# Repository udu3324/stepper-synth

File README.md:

# stepper-synth

An electronic instrument that uses stepper motors to make music. Powered by the esp32 ecosystem, it is a synthesizer with 3 octaves with velocity support using hall effect sensors. It is inspired by the musician/engineer [Love Hultén](https://www.youtube.com/@hulten1000).

## Why I Made This

There's so many electronic instruments that make sounds purely through cables and rely on other devices to output to them. Instead, what if I used the power of stepper motors to make sound and create a standalone device? I notice how harmonic these motors could be while 3d printing, they sometimes have a noticable pattern and variable pitch that can be utilized.

## Photos

## PCB

## Schematics

## Bill of Materials

Sadly I was aiming for tier 2 budget but didn't realize how much tariffs and shipping would push me out of it 😭

Interactive Link: [google sheets](https://docs.google.com/spreadsheets/d/12KobohwvsCrDZkVZn1qAy473UDQfyoO-3Iqs66wPygc/edit?usp=sharing)

|Part                     |Cost   |Count|Count Cost|Note                                                     |Status |Link                                                                                                                                                             |
|-------------------------|-------|-----|----------|---------------------------------------------------------|-------|-----------------------------------------------------------------------------------------------------------------------------------------------------------------|
|Regular Switches         |       |2    |0         |                                                         |On hand|https://divinikey.com/collections/linear-switches                                                                                                                |
|Hall Effect Switches     |$13.50 |2    |$27.00    |18x per                                                  |       |https://divinikey.com/collections/hall-effect-switches/products/gateron-magnetic-genty-he-switches                                                               |
|Rotary Encoder           |       |3    |0         |                                                         |On hand|https://www.mouser.com/ProductDetail/Alps-Alpine/EC11E183440C?qs=YMSFtX0bdJC6PoDF7K4k%252Bg%3D%3D                                                                |
|Button                   |       |1    |0         |                                                         |On hand|https://www.digikey.com/en/products/detail/te-connectivity-alcoswitch-switches/1825910-6/1632536                                                                 |
|WS2812                   |$0.80  |8    |$6.40     |neopixels                                                |       |https://www.mouser.com/ProductDetail/SparkFun/COM-24837?qs=dbcCsuKDzFUNFvBH5VYBTw%3D%3D                                                                          |
|LRS-350-24               |       |1    |0         |power supply                                             |On hand|https://www.digikey.com/en/products/detail/mean-well-usa-inc/LRS-350-24/7705034                                                                                  |
|IEC320 C14 Switch        |       |1    |0         |cable input                                              |On hand|https://www.aliexpress.us/item/3256804155743663.html                                                                                                             |
|Screw Terminal           |$0.35  |1    |$0.35     |                                                         |       |https://www.mouser.com/ProductDetail/Same-Sky/TB002-500-02BE?qs=vLWxofP3U2x9716kcgva%2Fw%3D%3D                                                                   |
|Nema 17 0.8 Motors       |       |4    |$0.00     |reused prusas                                            |On hand|https://www.omc-stepperonline.com/nema-17-bipolar-0-9deg-46ncm-65-1oz-in-2a-2-9v-42x42x48mm-4-wires-17hm19-2004s                                                 |
|ESP32-S3-WROOM-2         |$11.87 |1    |$11.87    |microcontroller                                          |       |https://www.mouser.com/ProductDetail/Espressif-Systems/ESP32-S3-WROOM-2-N32R16V?qs=%252BHhoWzUJg4Kf%2FwmS40wg%252BQ%3D%3D                                        |
|Solder Paste Syringe     |$16.95 |1    |$16.95    |mine dried out                                           |       |https://www.mouser.com/ProductDetail/Chip-Quik/TS391LT?qs=1mbolxNpo8dzjCIcP7S2Kg%3D%3D                                                                           |
|150uF Polarized Capacitor|$1.40  |4    |$5.60     |                                                         |       |https://www.mouser.com/ProductDetail/Panasonic/EEH-AZA1E151B?qs=sGAEpiMZZMsh%252B1woXyUXj7hTFrnMyX90Ysfyv/7vmlA%3D                                               |
|Female Pin Headers       |$0.84  |2    |$1.68     |                                                         |       |https://www.mouser.com/ProductDetail/Samtec/CES-102-02-G-S?qs=0lQeLiL1qyY%2FrwXtinpohw%3D%3D                                                                     |
|Hot-swap Switch Plug     |       |2    |0         |                                                         |On hand|https://www.gateron.com/products/gateron-low-profile-switch-hot-swap-pcb-socket?srsltid=AfmBOop0aFTt__A_sBY2D5LC6GJteiDSPO9H3qEt2M2Dhil_s2AUwsRR&VariantsId=10234|
|M3x5mm Screws            |       |18   |          |                                                         |On hand|https://www.moddiy.com/products/1264/M3.0-x-5mm-Black-Screws-(KM3X5).html?srsltid=AfmBOorXbTDS16CG3UQ8tCHJn64vKhPv2bQRUskhtAbTRuyfojuJ6yEs_D8                    |
|                         |       |     |          |                                                         |       |                                                                                                                                                                 |
|PCB Prototype            |$12.20 |     |          |                                                         |       |                                                                                                                                                                 |
|PCBA                     |$90.68 |     |          |6 extended parts only                                    |       |                                                                                                                                                                 |
|Merchandise Total        |$102.88|     |          |pcb + pcba                                               |       |                                                                                                                                                                 |
|Shipping Estimate        |$55.24 |     |          |                                                         |       |                                                                                                                                                                 |
|Duties & Taxes (US)      |$46.30 |     |          |                                                         |       |                                                                                                                                                                 |
|Sales Tax                |$13.04 |     |          |                                                         |       |                                                                                                                                                                 |
|Grand Total              |$217.46|     |          |only count this                                          |       |                                                                                                                                                                 |
|                         |       |     |          |                                                         |       |                                                                                                                                                                 |
|                         |$217.46|     |69.85     |                                                         |       |                                                                                                                                                                 |
|                         |       |     |          |                                                         |       |                                                                                                                                                                 |
|Needed for Grant         |$287.31|     |          |not including shipping and taxes from mouser/divinikey!!!|       |                                                                                                                                                                 |
|                         |       |     |          |though mouser shipping should be really low              |       |                                                                                                                                                                 |

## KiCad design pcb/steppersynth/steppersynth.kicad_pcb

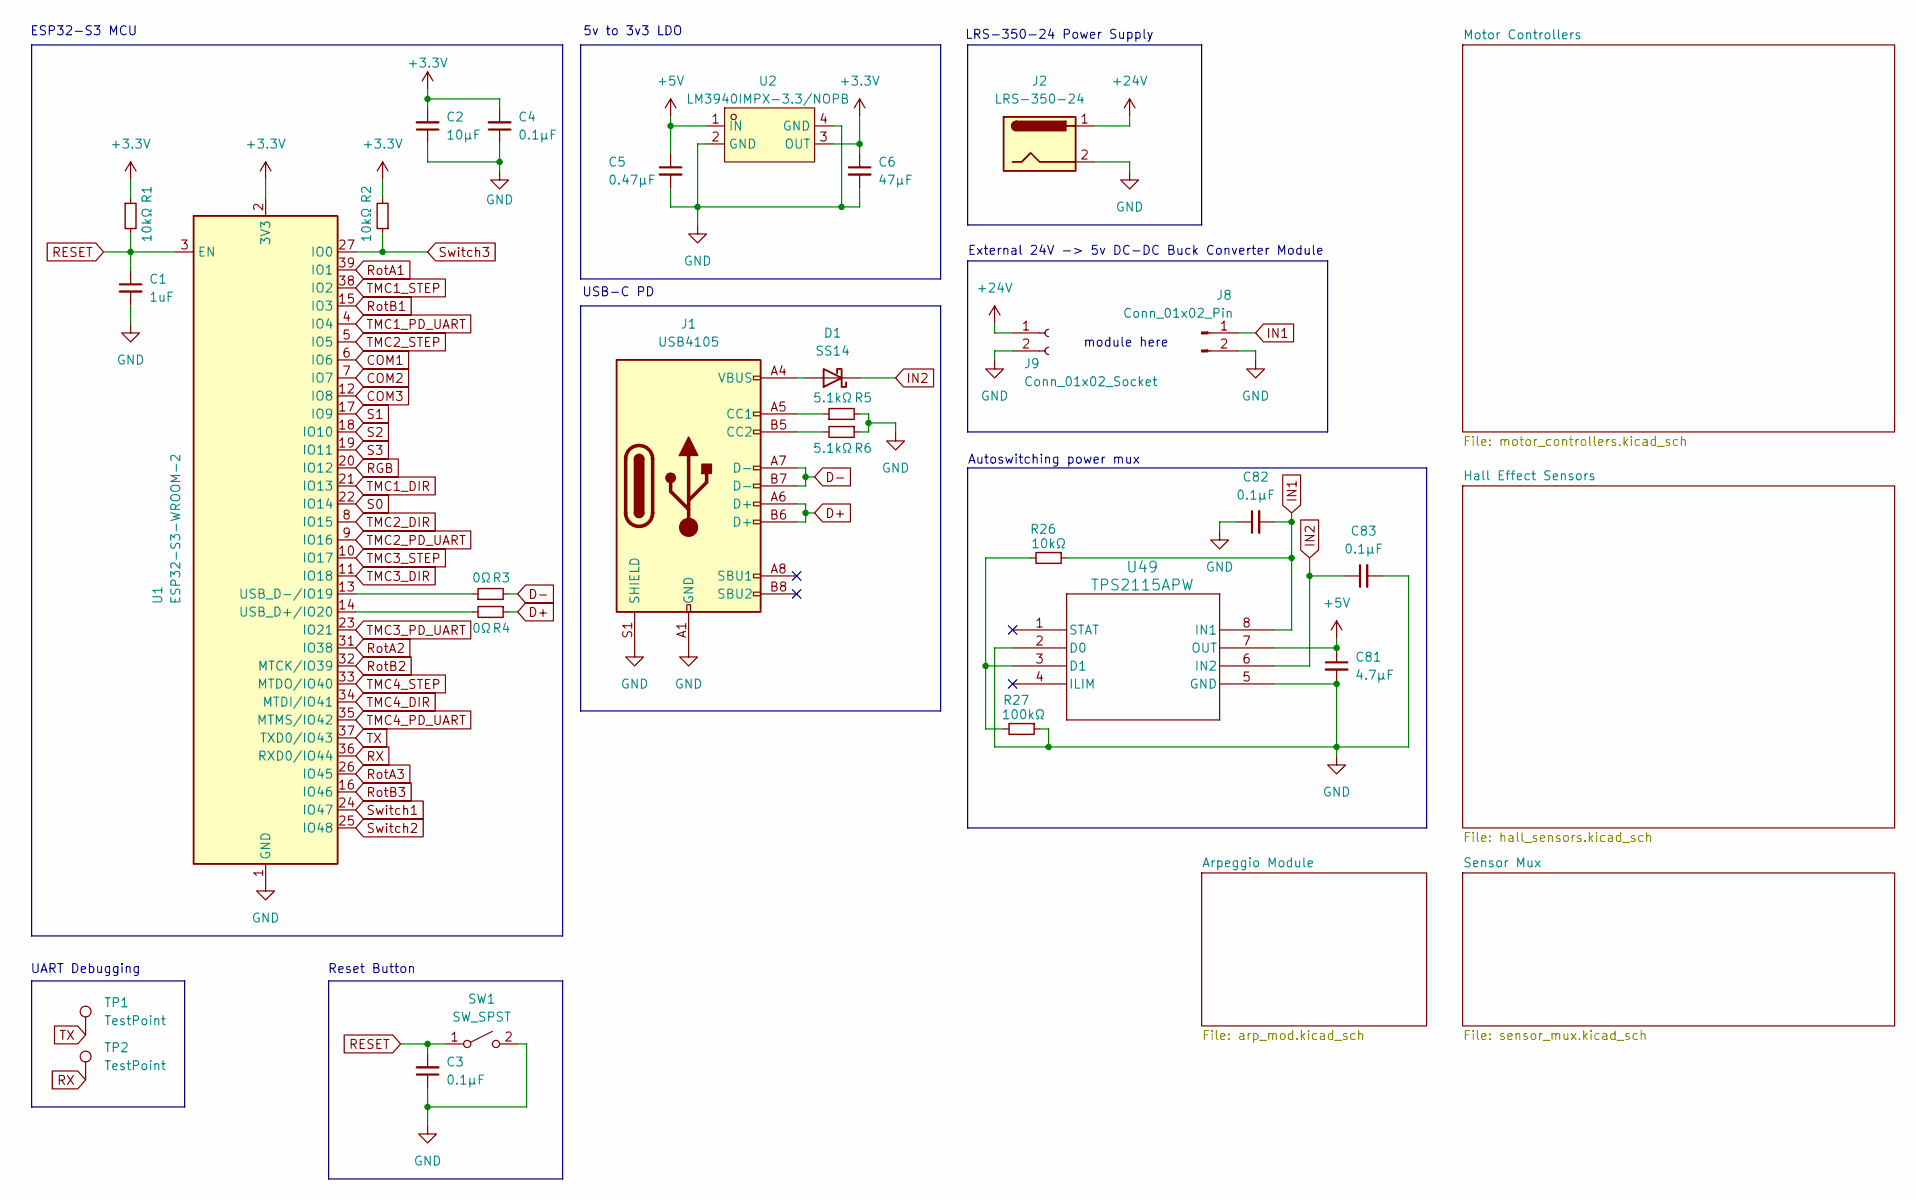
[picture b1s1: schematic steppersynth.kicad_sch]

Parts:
C1: 1uF; C_0805_2012Metric
C2: 10μF; C_0805_2012Metric
C3, C4, C82, C83: 0.1μF; C_0805_2012Metric
C5: 0.47μF; C_0805_2012Metric
C6: 47μF; C_0805_2012Metric
C81: 4.7μF; C_0805_2012Metric
D1: SS14; D_SMA
J1: USB4105; USB_C_Receptacle_GCT_USB4105-xx-A_16P_TopMnt_Horizontal
J2: LRS-350-24; TerminalBlock_MetzConnect_Type055_RT01502HDWU_1x02_P5.00mm_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
J8: Conn_01x02_Pin; PinSocket_1x02_P2.54mm_Vertical
J9: Conn_01x02_Socket; PinSocket_1x02_P2.54mm_Vertical
R1, R2, R26: 10kΩ; R_0805_2012Metric
R3, R4: 0Ω; R_0805_2012Metric
R5, R6: 5.1kΩ; R_0805_2012Metric
R27: 100kΩ; R_0805_2012Metric
SW1: SW_SPST; SW_PUSH_6mm
TP1, TP2: TestPoint; MountingHole_3.2mm_M3_Pad
U1: ESP32-S3-WROOM-2
U2: LM3940IMPX-3.3/NOPB; SOT-223-4_L6.5-W3.5-P2.30-LS7.0-BR; LCSC Part C544820
U49: TPS2115APW; PW8

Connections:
+3.3V: C2.2, C4.2, C6.1, R1.1, R2.2, U1.2 (3V3), U2.3 (OUT); also elsewhere on the board
+5V: C5.1, C81.1, U2.1 (IN), U49.7 (OUT); also elsewhere on the board
+24V: J2.1, J9.1; also elsewhere on the board
COM1: U1.6 (IO6); also elsewhere on the board
COM2: U1.7 (IO7); also elsewhere on the board
COM3: U1.12 (IO8); also elsewhere on the board
D+: J1.A6 (D+), J1.B6 (D+), R4.1
D-: J1.A7 (D-), J1.B7 (D-), R3.2
GND: C1.2, C2.1, C3.1, C4.1, C5.2, C6.2, C81.2, C82.1, C83.2, J1.A1 (GND), J1.A12 (GND), J1.B1 (GND), J1.B12 (GND), J1.S1 (SHIELD), J2.2, J8.2, J9.2, R5.2, R6.1, R27.1, SW1.2 (B), U1.1 (GND), U1.40 (GND), U1.41 (GND), U2.2 (GND), U2.4 (GND), U49.2 (D0), U49.5 (GND); also elsewhere on the board
IN1: C82.2, J8.1, R26.1, U49.8 (IN1)
IN2: C83.1, D1.1 (K), U49.6 (IN2)
unnamed: D1.2 (A), J1.A4 (VBUS), J1.A9 (VBUS), J1.B4 (VBUS), J1.B9 (VBUS)
unnamed: J1.A5 (CC1), R5.1
unnamed: J1.B5 (CC2), R6.2
unnamed: R4.2, U1.14 (USB_D+/IO20)
unnamed: R3.1, U1.13 (USB_D-/IO19)
unnamed: R26.2, R27.2, U49.3 (D1)
RESET: C1.1, C3.2, R1.2, SW1.1 (A), U1.3 (EN)
RGB: U1.20 (IO12); also elsewhere on the board
RX: TP2.1, U1.36 (RXD0/IO44)
RotA1: U1.39 (IO1); also elsewhere on the board
RotA2: U1.31 (IO38); also elsewhere on the board
RotA3: U1.26 (IO45); also elsewhere on the board
RotB1: U1.15 (IO3); also elsewhere on the board
RotB2: U1.32 (MTCK/IO39); also elsewhere on the board
RotB3: U1.16 (IO46); also elsewhere on the board
S0: U1.22 (IO14); also elsewhere on the board
S1: U1.17 (IO9); also elsewhere on the board
S2: U1.18 (IO10); also elsewhere on the board
S3: U1.19 (IO11); also elsewhere on the board
Switch1: U1.24 (IO47); also elsewhere on the board
Switch2: U1.25 (IO48); also elsewhere on the board
Switch3: R2.1, U1.27 (IO0); also elsewhere on the board
TMC1_DIR: U1.21 (IO13); also elsewhere on the board
TMC1_PD_UART: U1.4 (IO4); also elsewhere on the board
TMC1_STEP: U1.38 (IO2); also elsewhere on the board
TMC2_DIR: U1.8 (IO15); also elsewhere on the board
TMC2_PD_UART: U1.9 (IO16); also elsewhere on the board
TMC2_STEP: U1.5 (IO5); also elsewhere on the board
TMC3_DIR: U1.11 (IO18); also elsewhere on the board
TMC3_PD_UART: U1.23 (IO21); also elsewhere on the board
TMC3_STEP: U1.10 (IO17); also elsewhere on the board
TMC4_DIR: U1.34 (MTDI/IO41); also elsewhere on the board
TMC4_PD_UART: U1.35 (MTMS/IO42); also elsewhere on the board
TMC4_STEP: U1.33 (MTDO/IO40); also elsewhere on the board
TX: TP1.1, U1.37 (TXD0/IO43)

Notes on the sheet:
5v to 3v3 LDO
LRS-350-24 Power Supply
ESP32-S3 MCU
Reset Button
Autoswitching power mux
USB-C PD
module here
UART Debugging
External 24V -> 5v DC-DC Buck Converter Module

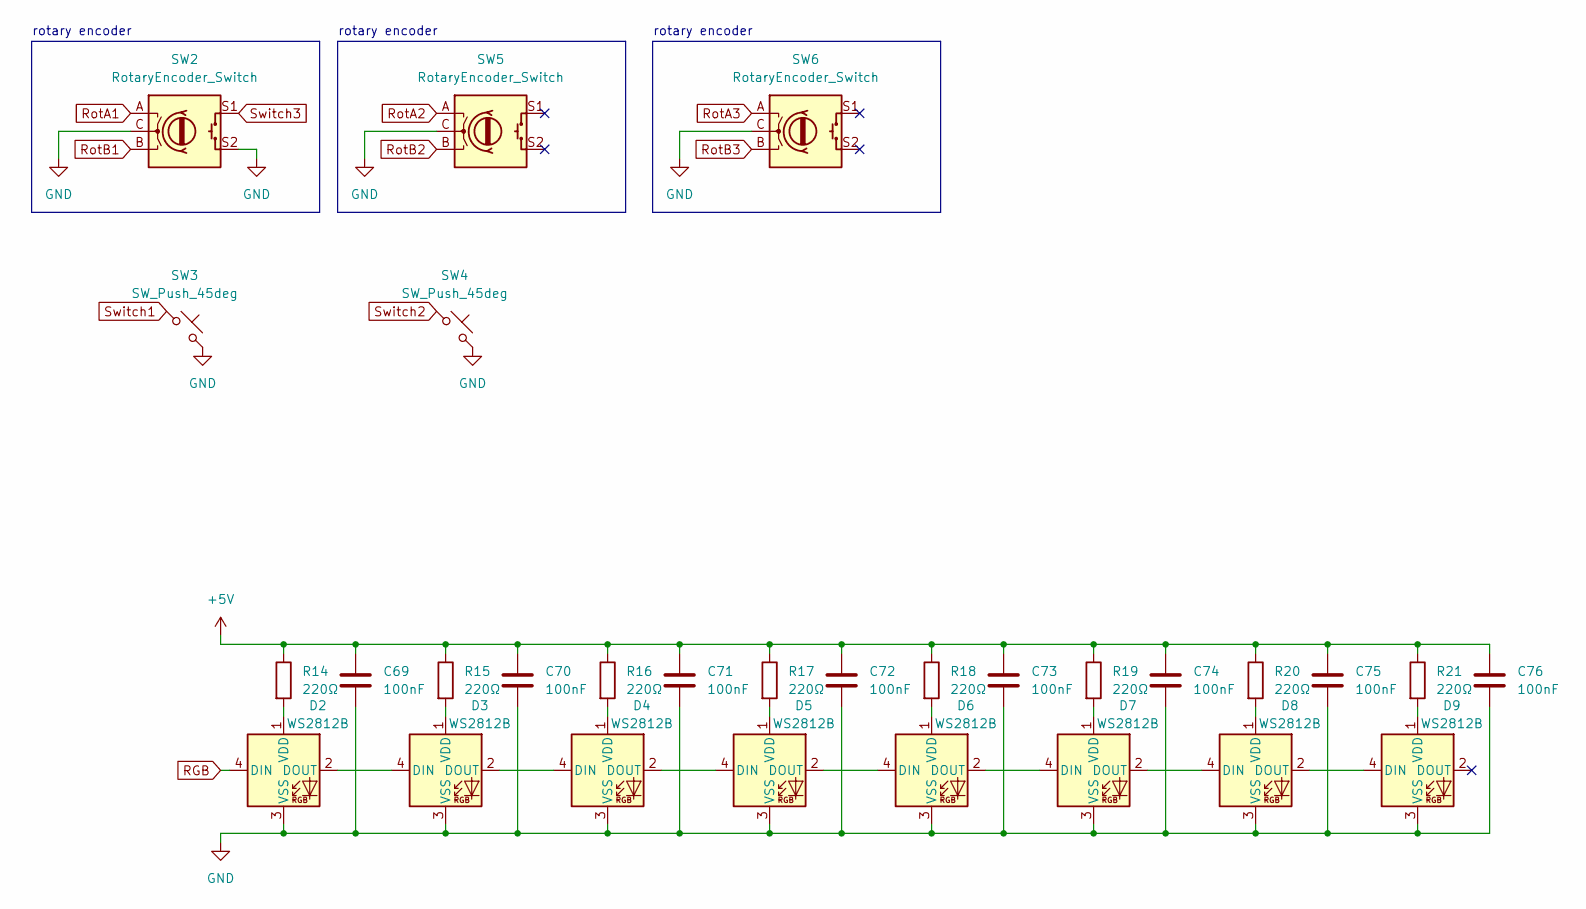
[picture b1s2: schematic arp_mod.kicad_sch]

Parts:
C69, C70, C71, C72, C73, C74, C75, C76: 100nF; C_0805_2012Metric
D2, D3, D4, D5, D6, D7, D8, D9: WS2812B; LED_WS2812B_PLCC4_5.0x5.0mm_P3.2mm
R14, R15, R16, R17, R18, R19, R20, R21: 220Ω; R_0805_2012Metric
SW2, SW5, SW6: RotaryEncoder_Switch; RotaryEncoder_Alps_EC11E-Switch_Vertical_H20mm
SW3, SW4: SW_Push_45deg; TH_L10.9-W5.9-CPG151101S11

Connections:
+5V: C69.1, C70.1, C71.1, C72.1, C73.1, C74.1, C75.1, C76.1, R14.1, R15.1, R16.1, R17.1, R18.1, R19.1, R20.1, R21.1; also elsewhere on the board
GND: C69.2, C70.2, C71.2, C72.2, C73.2, C74.2, C75.2, C76.2, D2.3 (VSS), D3.3 (VSS), D4.3 (VSS), D5.3 (VSS), D6.3 (VSS), D7.3 (VSS), D8.3 (VSS), D9.3 (VSS), SW2.C, SW2.S2, SW3.2, SW4.2, SW5.C, SW6.C; also elsewhere on the board
unnamed: D2.2 (DOUT), D3.4 (DIN)
unnamed: D2.1 (VDD), R14.2
unnamed: D3.2 (DOUT), D4.4 (DIN)
unnamed: D3.1 (VDD), R15.2
unnamed: D4.2 (DOUT), D5.4 (DIN)
unnamed: D4.1 (VDD), R16.2
unnamed: D5.2 (DOUT), D6.4 (DIN)
unnamed: D5.1 (VDD), R17.2
unnamed: D6.2 (DOUT), D7.4 (DIN)
unnamed: D6.1 (VDD), R18.2
unnamed: D7.2 (DOUT), D8.4 (DIN)
unnamed: D7.1 (VDD), R19.2
unnamed: D8.2 (DOUT), D9.4 (DIN)
unnamed: D8.1 (VDD), R20.2
unnamed: D9.1 (VDD), R21.2
RGB: D2.4 (DIN); also elsewhere on the board
RotA1: SW2.A; also elsewhere on the board
RotA2: SW5.A; also elsewhere on the board
RotA3: SW6.A; also elsewhere on the board
RotB1: SW2.B; also elsewhere on the board
RotB2: SW5.B; also elsewhere on the board
RotB3: SW6.B; also elsewhere on the board
Switch1: SW3.1; also elsewhere on the board
Switch2: SW4.1; also elsewhere on the board
Switch3: SW2.S1; also elsewhere on the board

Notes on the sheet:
rotary encoder

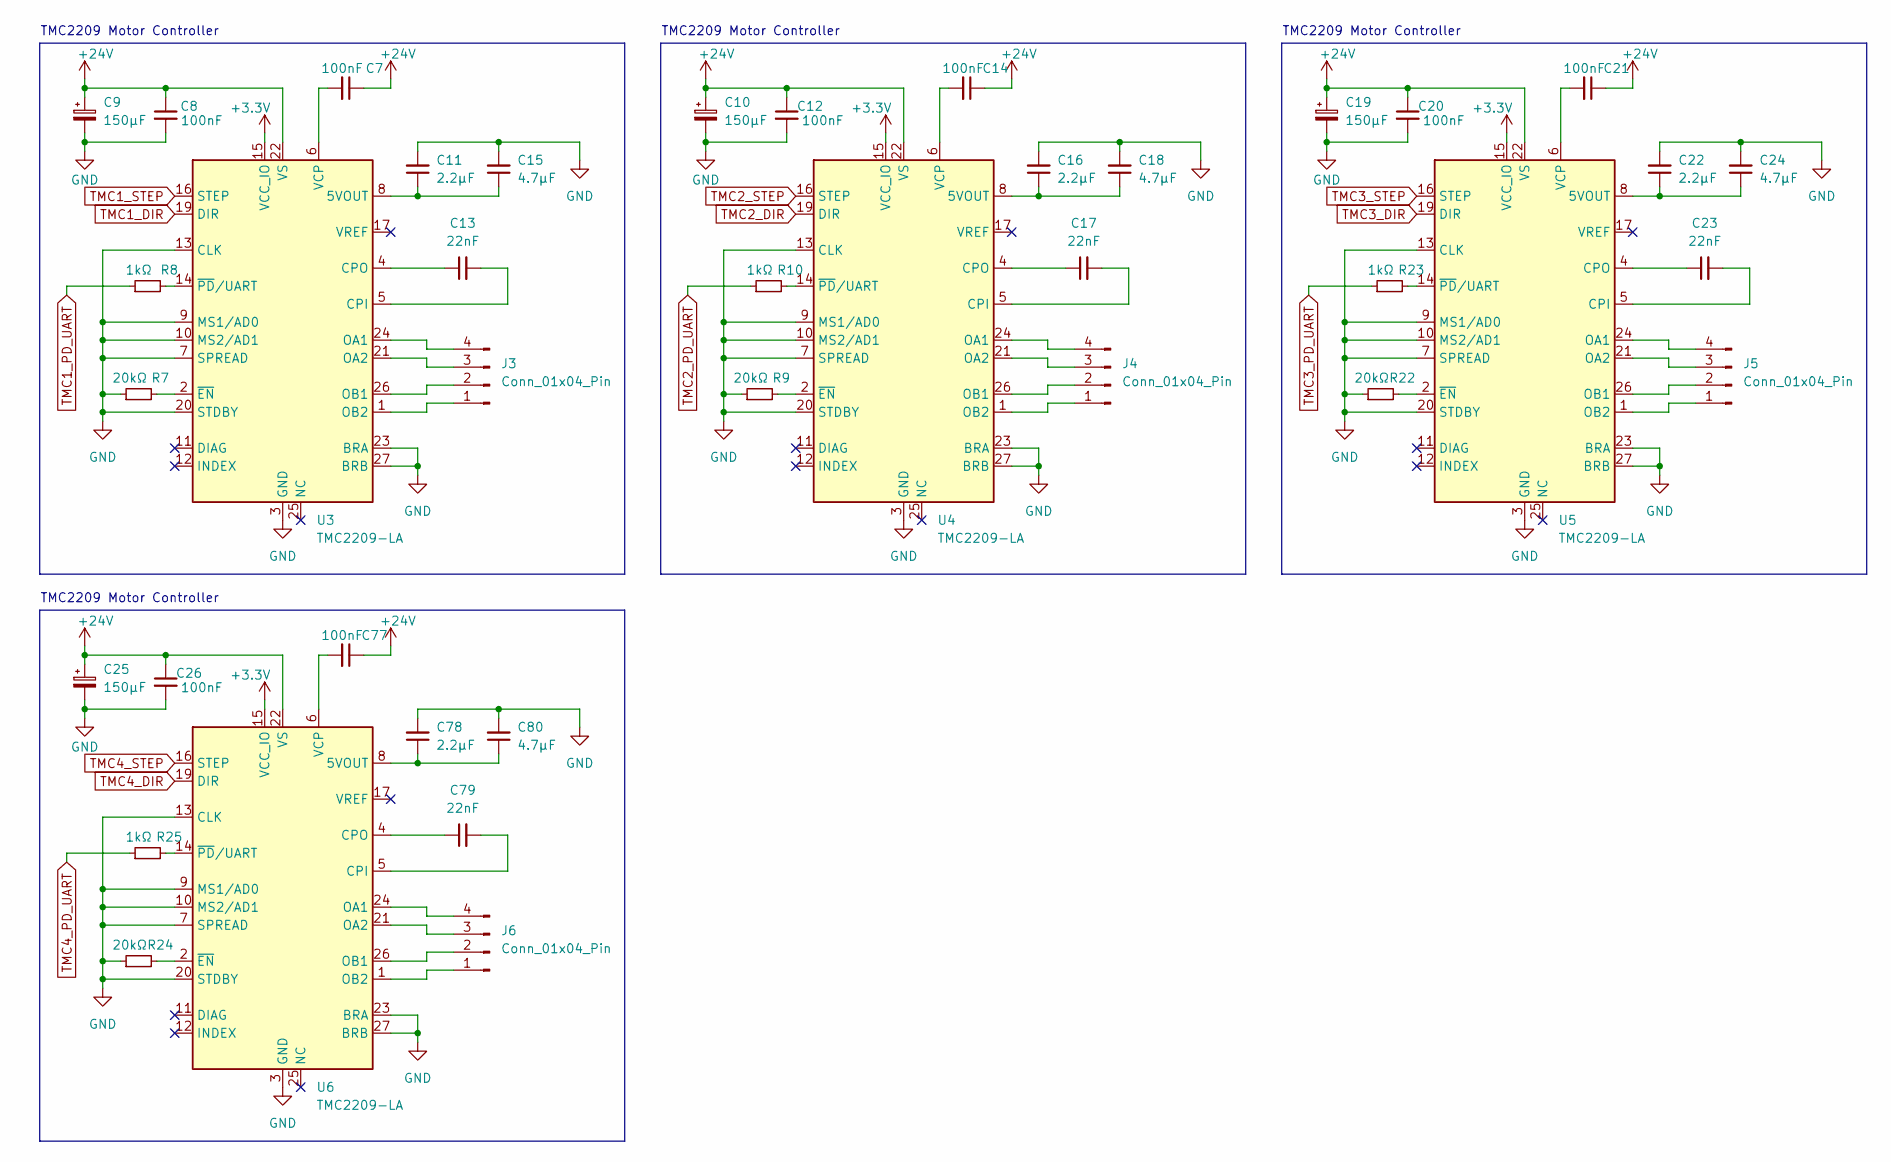
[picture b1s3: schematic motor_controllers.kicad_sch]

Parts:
C7, C8, C12, C14, C20, C21, C26, C77: 100nF; C_0805_2012Metric
C9, C10, C19, C25: 150µF; C_Radial_D10.0mm_H12.5mm_P5.00mm
C11, C16, C22, C78: 2.2µF; C_0805_2012Metric
C13, C17, C23, C79: 22nF; C_0805_2012Metric
C15, C18, C24, C80: 4.7µF; C_0805_2012Metric
J3, J4, J5, J6: Conn_01x04_Pin; PinHeader_1x04_P2.54mm_Vertical
R7, R9, R22, R24: 20kΩ; R_0805_2012Metric
R8, R10, R23, R25: 1kΩ; R_0805_2012Metric
U3, U4, U5, U6: TMC2209-LA; VQFN-28-1EP_5x5mm_P0.5mm_EP3.7x3.7mm_ThermalVias

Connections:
+3.3V: U3.15 (VCC_IO), U4.15 (VCC_IO), U5.15 (VCC_IO), U6.15 (VCC_IO); also elsewhere on the board
+24V: C7.1, C8.1, C9.1, C10.1, C12.1, C14.1, C19.1, C20.1, C21.1, C25.1, C26.1, C77.1, U3.22 (VS), U3.28 (VS), U4.22 (VS), U4.28 (VS), U5.22 (VS), U5.28 (VS), U6.22 (VS), U6.28 (VS); also elsewhere on the board
GND: C8.2, C9.2, C10.2, C11.2, C12.2, C15.2, C16.2, C18.2, C19.2, C20.2, C22.2, C24.2, C25.2, C26.2, C78.2, C80.2, R7.1, R9.1, R22.1, R24.1, U3.3 (GND), U3.7 (SPREAD), U3.9 (MS1/AD0), U3.10 (MS2/AD1), U3.13 (CLK), U3.18 (GND), U3.20 (STDBY), U3.23 (BRA), U3.27 (BRB), U3.29 (GND), U4.3 (GND), U4.7 (SPREAD), U4.9 (MS1/AD0), U4.10 (MS2/AD1), U4.13 (CLK), U4.18 (GND), U4.20 (STDBY), U4.23 (BRA), U4.27 (BRB), U4.29 (GND), U5.3 (GND), U5.7 (SPREAD), U5.9 (MS1/AD0), U5.10 (MS2/AD1), U5.13 (CLK), U5.18 (GND), U5.20 (STDBY), U5.23 (BRA), U5.27 (BRB), U5.29 (GND), U6.3 (GND), U6.7 (SPREAD), U6.9 (MS1/AD0), U6.10 (MS2/AD1), U6.13 (CLK), U6.18 (GND), U6.20 (STDBY), U6.23 (BRA), U6.27 (BRB), U6.29 (GND); also elsewhere on the board
unnamed: J3.1, U3.1 (OB2)
unnamed: J3.2, U3.26 (OB1)
unnamed: J3.3, U3.21 (OA2)
unnamed: J3.4, U3.24 (OA1)
unnamed: J4.1, U4.1 (OB2)
unnamed: J4.2, U4.26 (OB1)
unnamed: J4.3, U4.21 (OA2)
unnamed: J4.4, U4.24 (OA1)
unnamed: J5.1, U5.1 (OB2)
unnamed: J5.2, U5.26 (OB1)
unnamed: J5.3, U5.21 (OA2)
unnamed: J5.4, U5.24 (OA1)
unnamed: J6.1, U6.1 (OB2)
unnamed: J6.2, U6.26 (OB1)
unnamed: J6.3, U6.21 (OA2)
unnamed: J6.4, U6.24 (OA1)
unnamed: C11.1, C15.1, U3.8 (5VOUT)
unnamed: C13.2, U3.5 (CPI)
unnamed: C13.1, U3.4 (CPO)
unnamed: C7.2, U3.6 (VCP)
unnamed: R7.2, U3.2 (~EN)
unnamed: R8.2, U3.14 (~PD/UART)
unnamed: C16.1, C18.1, U4.8 (5VOUT)
unnamed: C17.2, U4.5 (CPI)
unnamed: C17.1, U4.4 (CPO)
unnamed: C14.2, U4.6 (VCP)
unnamed: R9.2, U4.2 (~EN)
unnamed: R10.2, U4.14 (~PD/UART)
unnamed: C22.1, C24.1, U5.8 (5VOUT)
unnamed: C23.2, U5.5 (CPI)
unnamed: C23.1, U5.4 (CPO)
unnamed: C21.2, U5.6 (VCP)
unnamed: R22.2, U5.2 (~EN)
unnamed: R23.2, U5.14 (~PD/UART)
unnamed: C78.1, C80.1, U6.8 (5VOUT)
unnamed: C79.2, U6.5 (CPI)
unnamed: C79.1, U6.4 (CPO)
unnamed: C77.2, U6.6 (VCP)
unnamed: R24.2, U6.2 (~EN)
unnamed: R25.2, U6.14 (~PD/UART)
TMC1_DIR: U3.19 (DIR); also elsewhere on the board
TMC1_PD_UART: R8.1; also elsewhere on the board
TMC1_STEP: U3.16 (STEP); also elsewhere on the board
TMC2_DIR: U4.19 (DIR); also elsewhere on the board
TMC2_PD_UART: R10.1; also elsewhere on the board
TMC2_STEP: U4.16 (STEP); also elsewhere on the board
TMC3_DIR: U5.19 (DIR); also elsewhere on the board
TMC3_PD_UART: R23.1; also elsewhere on the board
TMC3_STEP: U5.16 (STEP); also elsewhere on the board
TMC4_DIR: U6.19 (DIR); also elsewhere on the board
TMC4_PD_UART: R25.1; also elsewhere on the board
TMC4_STEP: U6.16 (STEP); also elsewhere on the board

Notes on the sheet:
TMC2209 Motor Controller

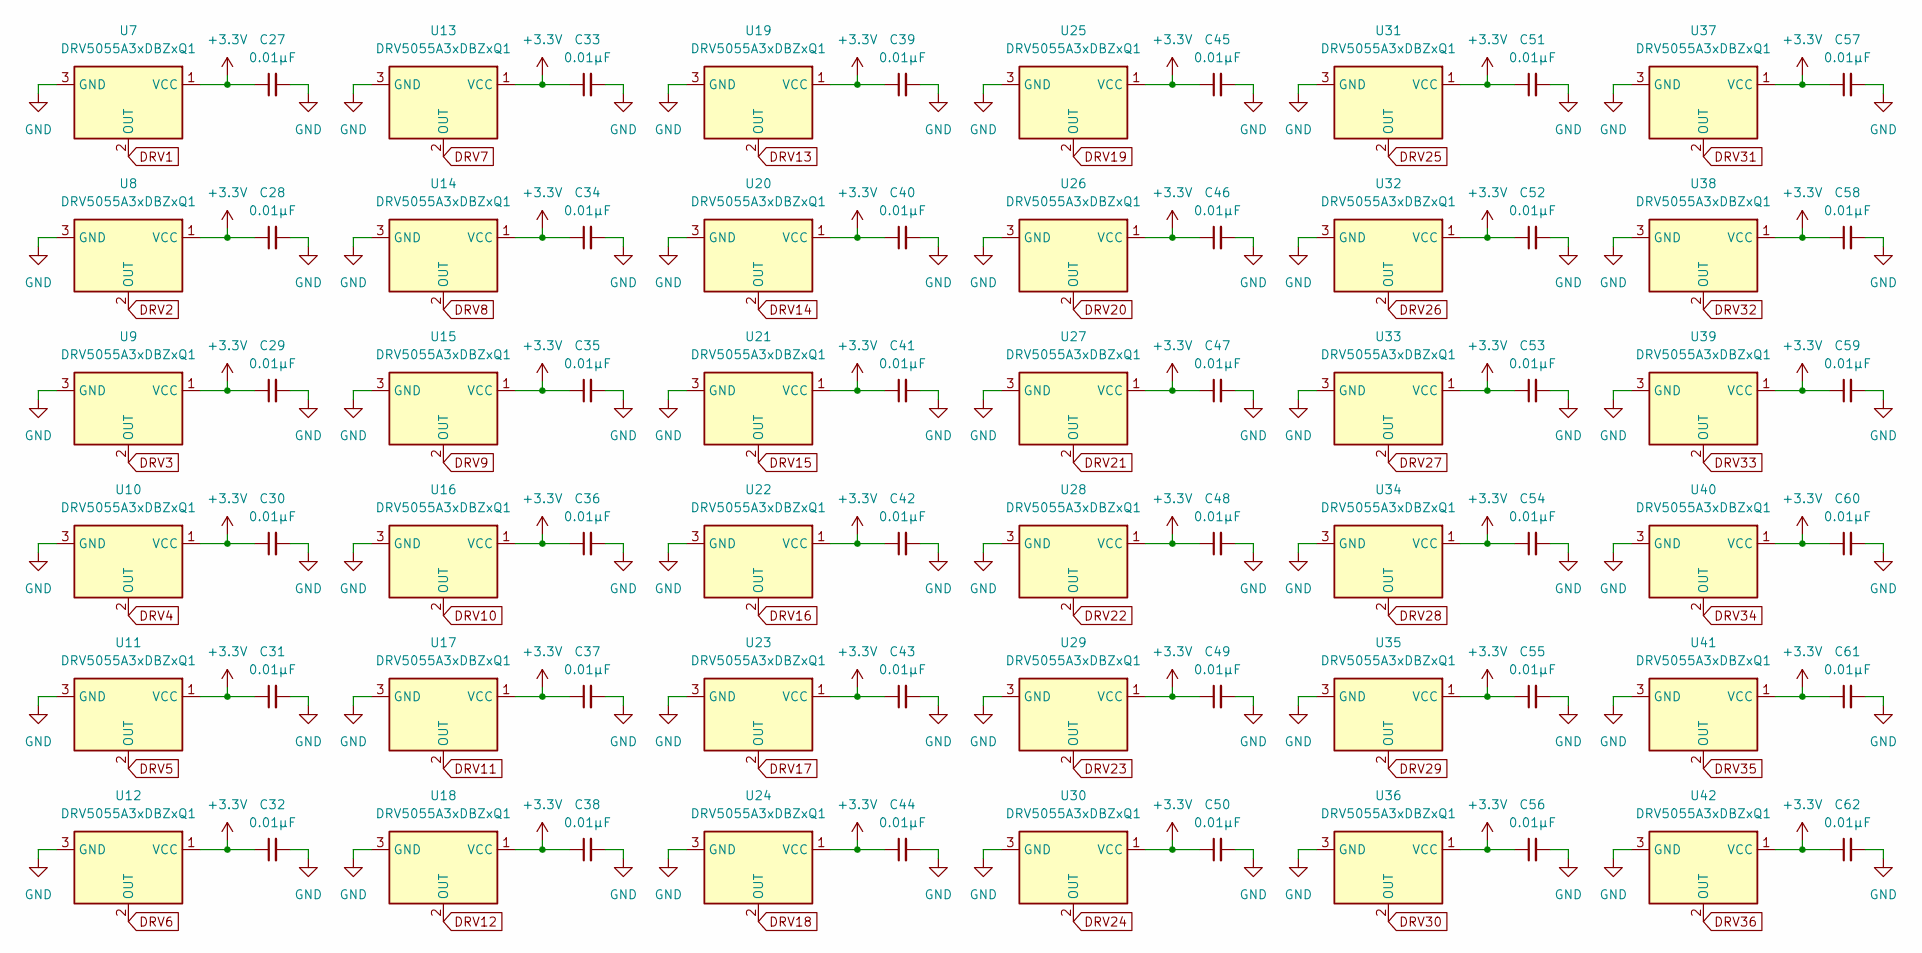
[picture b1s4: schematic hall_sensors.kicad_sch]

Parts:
C27, C28, C29, C30, C31, C32, C33, C34, C35, C36, C37, C38, C39, C40, C41, C42, C43, C44, C45, C46, C47, C48, C49, C50, C51, C52, C53, C54, C55, C56, C57, C58, C59, C60, C61, C62: 0.01µF; C_0805_2012Metric
U7, U8, U9, U10, U11, U12, U13, U14, U15, U16, U17, U18, U19, U20, U21, U22, U23, U24, U25, U26, U27, U28, U29, U30, U31, U32, U33, U34, U35, U36, U37, U38, U39, U40, U41, U42: DRV5055A3xDBZxQ1; SOT-23

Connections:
+3.3V: C27.1, C28.1, C29.1, C30.1, C31.1, C32.1, C33.1, C34.1, C35.1, C36.1, C37.1, C38.1, C39.1, C40.1, C41.1, C42.1, C43.1, C44.1, C45.1, C46.1, C47.1, C48.1, C49.1, C50.1, C51.1, C52.1, C53.1, C54.1, C55.1, C56.1, C57.1, C58.1, C59.1, C60.1, C61.1, C62.1, U7.1 (VCC), U8.1 (VCC), U9.1 (VCC), U10.1 (VCC), U11.1 (VCC), U12.1 (VCC), U13.1 (VCC), U14.1 (VCC), U15.1 (VCC), U16.1 (VCC), U17.1 (VCC), U18.1 (VCC), U19.1 (VCC), U20.1 (VCC), U21.1 (VCC), U22.1 (VCC), U23.1 (VCC), U24.1 (VCC), U25.1 (VCC), U26.1 (VCC), U27.1 (VCC), U28.1 (VCC), U29.1 (VCC), U30.1 (VCC), U31.1 (VCC), U32.1 (VCC), U33.1 (VCC), U34.1 (VCC), U35.1 (VCC), U36.1 (VCC), U37.1 (VCC), U38.1 (VCC), U39.1 (VCC), U40.1 (VCC), U41.1 (VCC), U42.1 (VCC); also elsewhere on the board
DRV1: U7.2 (OUT); also elsewhere on the board
DRV2: U8.2 (OUT); also elsewhere on the board
DRV3: U9.2 (OUT); also elsewhere on the board
DRV4: U10.2 (OUT); also elsewhere on the board
DRV5: U11.2 (OUT); also elsewhere on the board
DRV6: U12.2 (OUT); also elsewhere on the board
DRV7: U13.2 (OUT); also elsewhere on the board
DRV8: U14.2 (OUT); also elsewhere on the board
DRV9: U15.2 (OUT); also elsewhere on the board
DRV10: U16.2 (OUT); also elsewhere on the board
DRV11: U17.2 (OUT); also elsewhere on the board
DRV12: U18.2 (OUT); also elsewhere on the board
DRV13: U19.2 (OUT); also elsewhere on the board
DRV14: U20.2 (OUT); also elsewhere on the board
DRV15: U21.2 (OUT); also elsewhere on the board
DRV16: U22.2 (OUT); also elsewhere on the board
DRV17: U23.2 (OUT); also elsewhere on the board
DRV18: U24.2 (OUT); also elsewhere on the board
DRV19: U25.2 (OUT); also elsewhere on the board
DRV20: U26.2 (OUT); also elsewhere on the board
DRV21: U27.2 (OUT); also elsewhere on the board
DRV22: U28.2 (OUT); also elsewhere on the board
DRV23: U29.2 (OUT); also elsewhere on the board
DRV24: U30.2 (OUT); also elsewhere on the board
DRV25: U31.2 (OUT); also elsewhere on the board
DRV26: U32.2 (OUT); also elsewhere on the board
DRV27: U33.2 (OUT); also elsewhere on the board
DRV28: U34.2 (OUT); also elsewhere on the board
DRV29: U35.2 (OUT); also elsewhere on the board
DRV30: U36.2 (OUT); also elsewhere on the board
DRV31: U37.2 (OUT); also elsewhere on the board
DRV32: U38.2 (OUT); also elsewhere on the board
DRV33: U39.2 (OUT); also elsewhere on the board
DRV34: U40.2 (OUT); also elsewhere on the board
DRV35: U41.2 (OUT); also elsewhere on the board
DRV36: U42.2 (OUT); also elsewhere on the board
GND: C27.2, C28.2, C29.2, C30.2, C31.2, C32.2, C33.2, C34.2, C35.2, C36.2, C37.2, C38.2, C39.2, C40.2, C41.2, C42.2, C43.2, C44.2, C45.2, C46.2, C47.2, C48.2, C49.2, C50.2, C51.2, C52.2, C53.2, C54.2, C55.2, C56.2, C57.2, C58.2, C59.2, C60.2, C61.2, C62.2, U7.3 (GND), U8.3 (GND), U9.3 (GND), U10.3 (GND), U11.3 (GND), U12.3 (GND), U13.3 (GND), U14.3 (GND), U15.3 (GND), U16.3 (GND), U17.3 (GND), U18.3 (GND), U19.3 (GND), U20.3 (GND), U21.3 (GND), U22.3 (GND), U23.3 (GND), U24.3 (GND), U25.3 (GND), U26.3 (GND), U27.3 (GND), U28.3 (GND), U29.3 (GND), U30.3 (GND), U31.3 (GND), U32.3 (GND), U33.3 (GND), U34.3 (GND), U35.3 (GND), U36.3 (GND), U37.3 (GND), U38.3 (GND), U39.3 (GND), U40.3 (GND), U41.3 (GND), U42.3 (GND); also elsewhere on the board

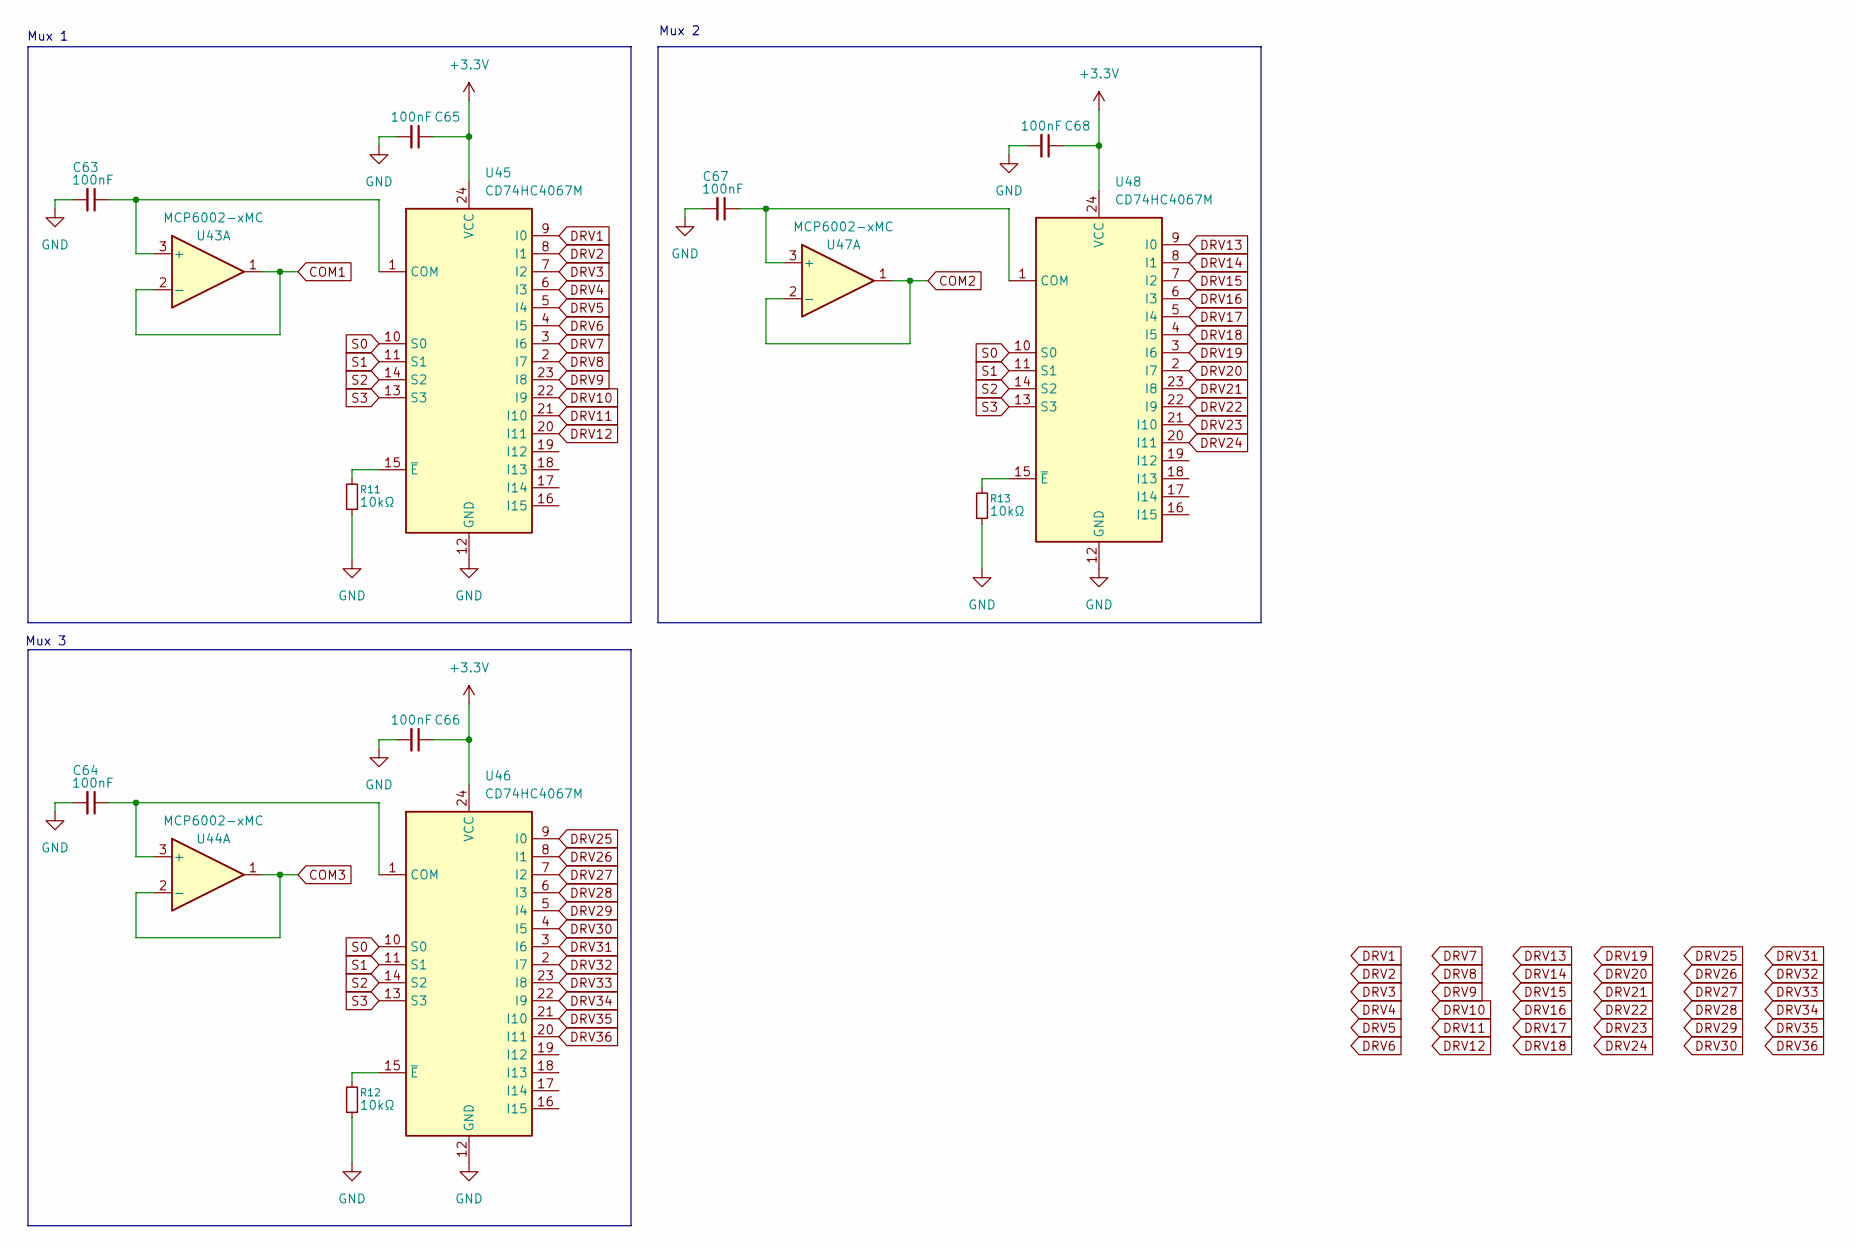
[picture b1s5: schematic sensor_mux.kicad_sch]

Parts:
C63, C64, C65, C66, C67, C68: 100nF; C_0805_2012Metric
R11, R12, R13: 10kΩ; R_0805_2012Metric
U43, U44, U47: MCP6002-xMC; DFN-8-1EP_3x2mm_P0.5mm_EP1.75x1.45mm
U45, U46, U48: CD74HC4067M; SOIC-24W_7.5x15.4mm_P1.27mm

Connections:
+3.3V: C65.1, C66.1, C68.1, U45.24 (VCC), U46.24 (VCC), U48.24 (VCC); also elsewhere on the board
COM1: U43.1, U43.2 (-); also elsewhere on the board
COM2: U47.1, U47.2 (-); also elsewhere on the board
COM3: U44.1, U44.2 (-); also elsewhere on the board
DRV1: U45.9 (I0); also elsewhere on the board
DRV2: U45.8 (I1); also elsewhere on the board
DRV3: U45.7 (I2); also elsewhere on the board
DRV4: U45.6 (I3); also elsewhere on the board
DRV5: U45.5 (I4); also elsewhere on the board
DRV6: U45.4 (I5); also elsewhere on the board
DRV7: U45.3 (I6); also elsewhere on the board
DRV8: U45.2 (I7); also elsewhere on the board
DRV9: U45.23 (I8); also elsewhere on the board
DRV10: U45.22 (I9); also elsewhere on the board
DRV11: U45.21 (I10); also elsewhere on the board
DRV12: U45.20 (I11); also elsewhere on the board
DRV13: U48.9 (I0); also elsewhere on the board
DRV14: U48.8 (I1); also elsewhere on the board
DRV15: U48.7 (I2); also elsewhere on the board
DRV16: U48.6 (I3); also elsewhere on the board
DRV17: U48.5 (I4); also elsewhere on the board
DRV18: U48.4 (I5); also elsewhere on the board
DRV19: U48.3 (I6); also elsewhere on the board
DRV20: U48.2 (I7); also elsewhere on the board
DRV21: U48.23 (I8); also elsewhere on the board
DRV22: U48.22 (I9); also elsewhere on the board
DRV23: U48.21 (I10); also elsewhere on the board
DRV24: U48.20 (I11); also elsewhere on the board
DRV25: U46.9 (I0); also elsewhere on the board
DRV26: U46.8 (I1); also elsewhere on the board
DRV27: U46.7 (I2); also elsewhere on the board
DRV28: U46.6 (I3); also elsewhere on the board
DRV29: U46.5 (I4); also elsewhere on the board
DRV30: U46.4 (I5); also elsewhere on the board
DRV31: U46.3 (I6); also elsewhere on the board
DRV32: U46.2 (I7); also elsewhere on the board
DRV33: U46.23 (I8); also elsewhere on the board
DRV34: U46.22 (I9); also elsewhere on the board
DRV35: U46.21 (I10); also elsewhere on the board
DRV36: U46.20 (I11); also elsewhere on the board
GND: C63.2, C64.2, C65.2, C66.2, C67.2, C68.2, R11.1, R12.1, R13.1, U45.12 (GND), U46.12 (GND), U48.12 (GND); also elsewhere on the board
unnamed: C63.1, U43.3 (+), U45.1 (COM)
unnamed: C64.1, U44.3 (+), U46.1 (COM)
unnamed: R11.2, U45.15 (~E)
unnamed: R12.2, U46.15 (~E)
unnamed: C67.1, U47.3 (+), U48.1 (COM)
unnamed: R13.2, U48.15 (~E)
S0: U45.10 (S0), U46.10 (S0), U48.10 (S0); also elsewhere on the board
S1: U45.11 (S1), U46.11 (S1), U48.11 (S1); also elsewhere on the board
S2: U45.14 (S2), U46.14 (S2), U48.14 (S2); also elsewhere on the board
S3: U45.13 (S3), U46.13 (S3), U48.13 (S3); also elsewhere on the board

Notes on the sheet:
Mux 3
Mux 1
Mux 2
